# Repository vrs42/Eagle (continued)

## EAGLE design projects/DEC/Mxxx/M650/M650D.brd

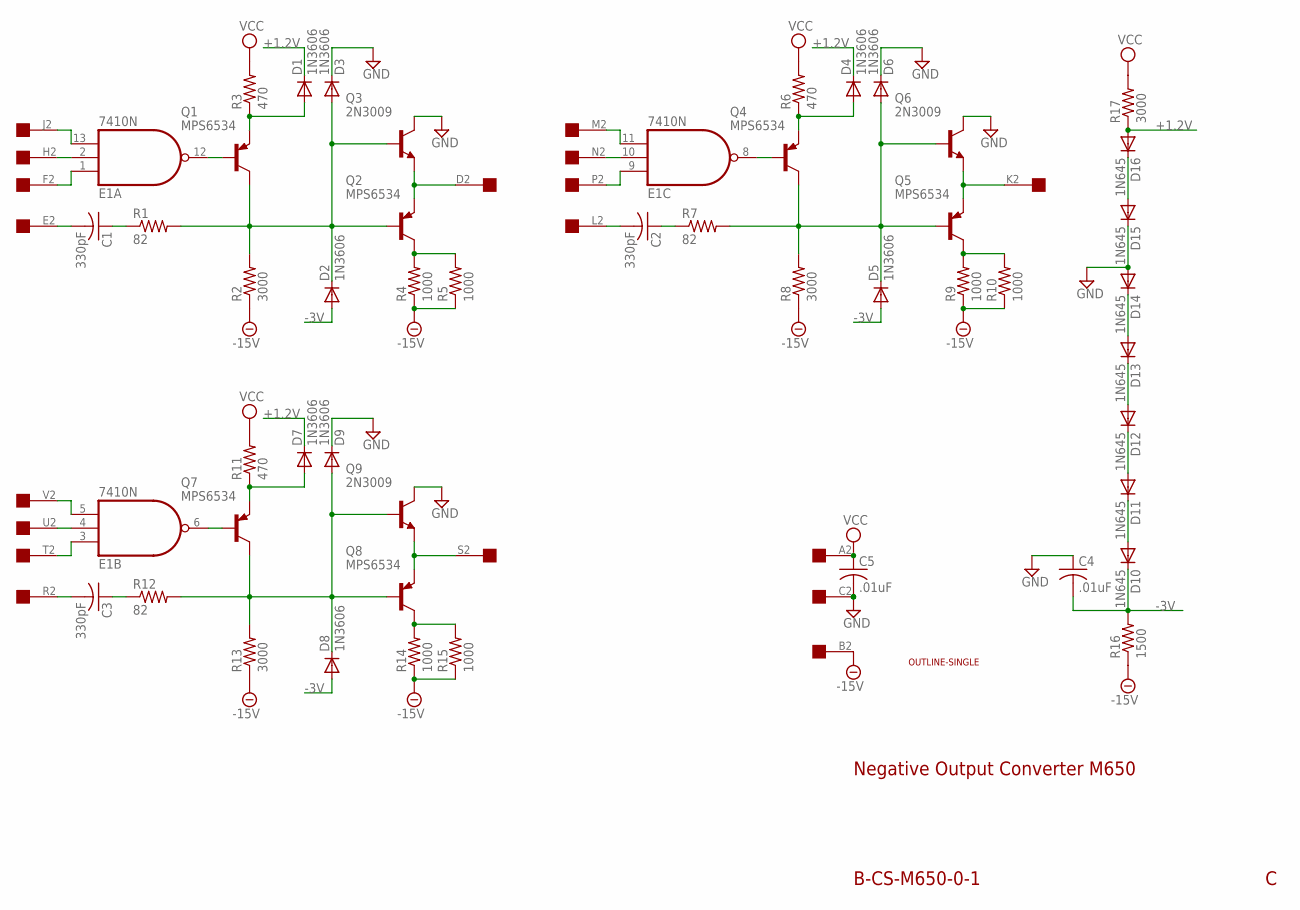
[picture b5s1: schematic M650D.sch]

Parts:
C1, C2, C3: 330pF; C050-025X075
C4, C5: .01uF; C050-025X075
D1, D2, D3, D4, D5, D6, D7, D8, D9: 1N3606; DO35-10
D10, D11, D12, D13, D14, D15, D16: 1N645; DO35-10
E1: 7410N; DIL14
Q1, Q2, Q4, Q5, Q7, Q8: MPS6534; TO39
Q3, Q6, Q9: 2N3009; TO5
R1, R7, R12: 82; 0207/10
R2, R8, R13, R17: 3000; 0207/10
R3, R6, R11: 470; 0207/10
R4, R5, R9, R10, R14, R15: 1000; 0207/10
R16: 1500; 0207/10
U$1: OUTLINE-SINGLE; SINGLE
U$3: EDGE-1; EDGE-CON1

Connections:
+1.2V: D1.C, D4.C, D7.C, D16.A, R17.1
-3V: C4.2, D2.A, D5.A, D8.A, D10.C, R16.2
-15V: R2.1, R4.1, R5.1, R8.1, R9.1, R10.1, R13.1, R14.1, R15.1, R16.1, U$3.B2
GND: C4.1, C5.2, D3.C, D6.C, D9.C, D14.A, D15.C, E1.7 (GND), Q3.3 (C), Q6.3 (C), Q9.3 (C), U$3.C2
unnamed: E1.2 (I1), U$3.H2
unnamed: C1.2, U$3.E2
unnamed: C1.1, R1.1
unnamed: E1.12 (O), Q1.2 (B)
unnamed: D1.A, Q1.1 (E), R3.1
unnamed: D2.C, D3.A, Q1.3 (C), Q2.2 (B), Q3.2 (B), R1.2, R2.2
unnamed: Q2.1 (E), Q3.1 (E), U$3.D2
unnamed: Q2.3 (C), R4.2, R5.2
unnamed: E1.9 (I0), U$3.P2
unnamed: E1.11 (I2), U$3.M2
unnamed: E1.10 (I1), U$3.N2
unnamed: E1.8 (O), Q4.2 (B)
unnamed: D4.A, Q4.1 (E), R6.1
unnamed: E1.1 (I0), U$3.F2
unnamed: E1.13 (I2), U$3.J2
unnamed: C2.2, U$3.L2
unnamed: C2.1, R7.1
unnamed: D5.C, D6.A, Q4.3 (C), Q5.2 (B), Q6.2 (B), R7.2, R8.2
unnamed: Q5.1 (E), Q6.1 (E), U$3.K2
unnamed: Q5.3 (C), R9.2, R10.2
unnamed: E1.3 (I0), U$3.T2
unnamed: E1.5 (I2), U$3.V2
unnamed: E1.4 (I1), U$3.U2
unnamed: E1.6 (O), Q7.2 (B)
unnamed: D7.A, Q7.1 (E), R11.1
unnamed: C3.2, U$3.R2
unnamed: C3.1, R12.1
unnamed: D8.C, D9.A, Q7.3 (C), Q8.2 (B), Q9.2 (B), R12.2, R13.2
unnamed: Q8.1 (E), Q9.1 (E), U$3.S2
unnamed: Q8.3 (C), R14.2, R15.2
unnamed: D10.A, D11.C
unnamed: D11.A, D12.C
unnamed: D12.A, D13.C
unnamed: D13.A, D14.C
unnamed: D15.A, D16.C
VCC: C5.1, E1.14 (VCC), R3.2, R6.2, R11.2, R17.2, U$3.A2

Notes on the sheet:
Negative Output Converter M650
B-CS-M650-0-1

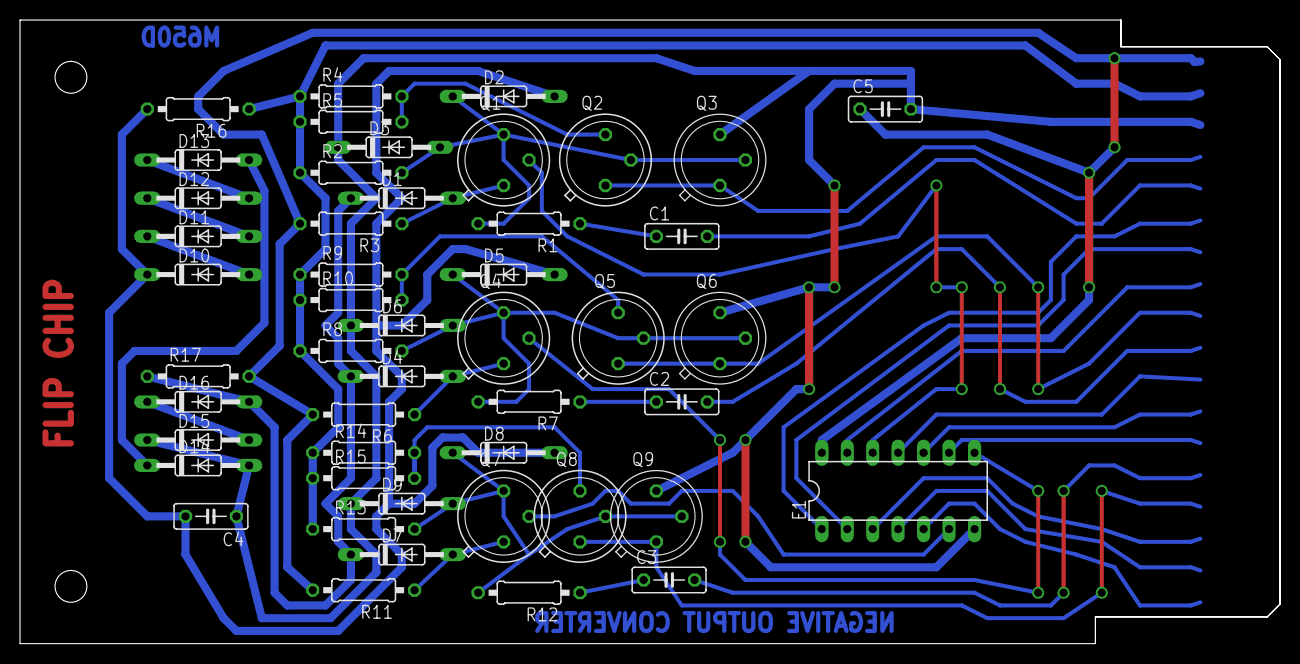
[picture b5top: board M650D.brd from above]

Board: 2 copper layers, 125.7 x 62.2 mm, 51 parts (0 on the bottom side), 40 nets.

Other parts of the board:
U$2: FLIPCHIP
